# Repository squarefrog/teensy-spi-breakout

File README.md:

# Teensy 3.2 SPI Breakout Board

A 45x42mm breakout board for the [Teensy 3.2](https://www.pjrc.com/teensy/teensy31.html). It features a tonne of `3V` and `GND` pins, as well as 3 header pins for SPI connections. There are smaller more concise breakouts, but I needed something that placed the Teensy's USB port at the top, with 4 decent sized mount points.

As used in my [MIDI Encoder Box](https://github.com/squarefrog/teensy-midi-encoder-box) project.

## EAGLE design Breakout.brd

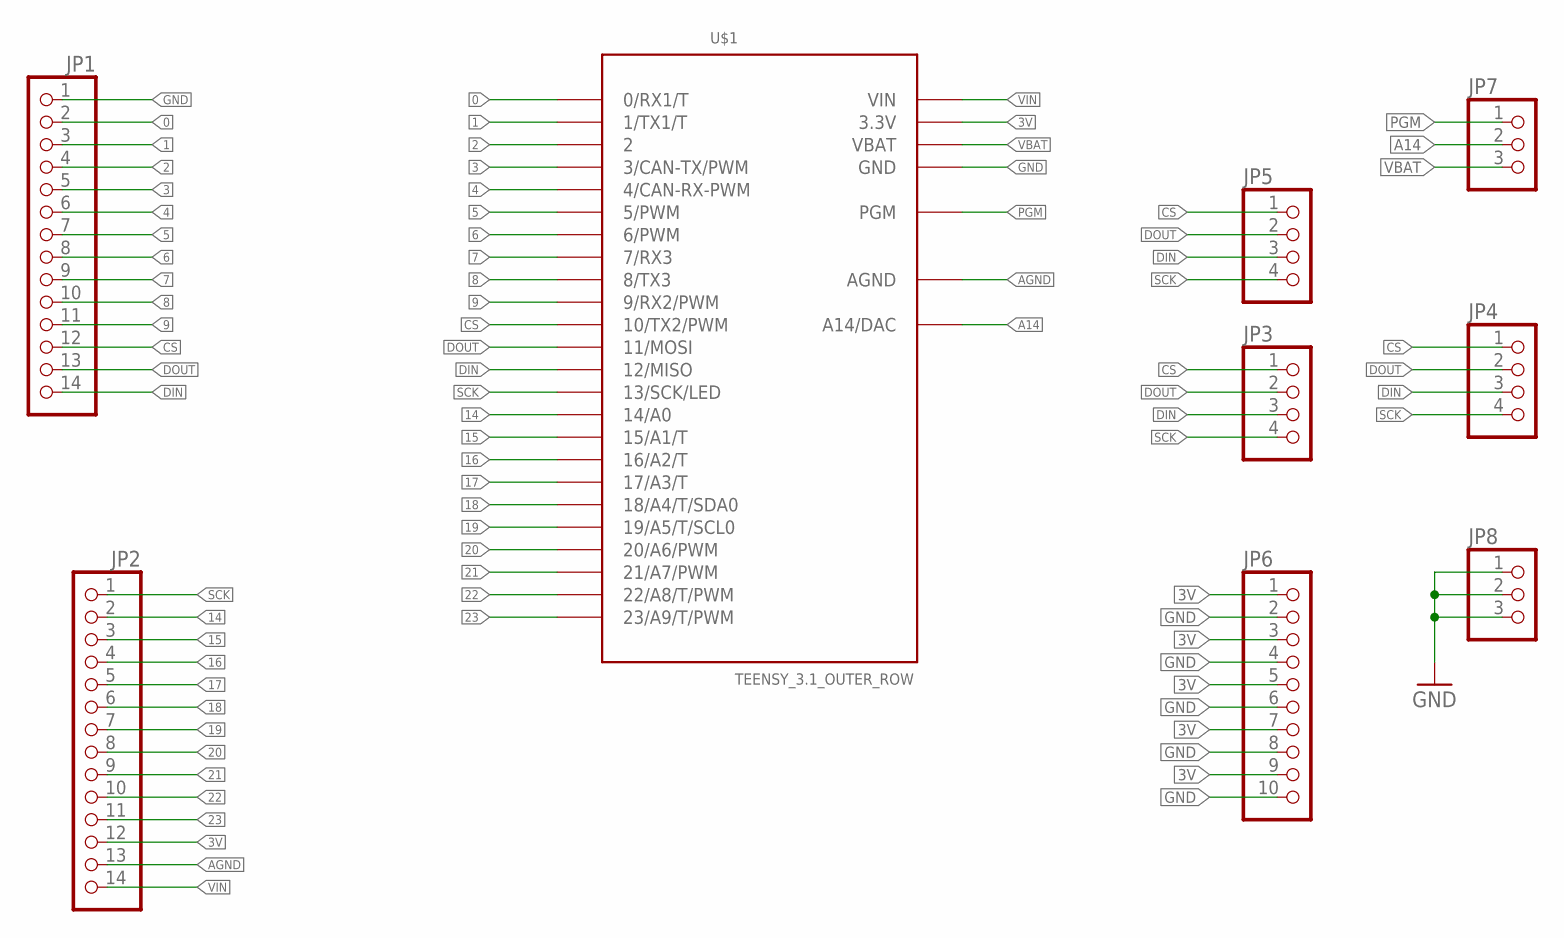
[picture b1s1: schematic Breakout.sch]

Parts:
JP1, JP2: PINHD-1X14; 1X14
JP3, JP4, JP5: PINHD-1X4; 1X04
JP6: PINHD-1X10; 1X10
JP7, JP8: PINHD-1X3; 1X03
U$1: TEENSY_3.1_OUTER_ROW; TEENSY3-OUTER_ROW

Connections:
0: JP1.2, U$1.0 (0/RX1/T)
1: JP1.3, U$1.1 (1/TX1/T)
2: JP1.4, U$1.2
3: JP1.5, U$1.3 (3/CAN-TX/PWM)
3V: JP2.12, JP6.1, JP6.3, JP6.5, JP6.7, JP6.9, U$1.3.3V, U$1.3.3V1 (3.3V)
4: JP1.6, U$1.4 (4/CAN-RX-PWM)
5: JP1.7, U$1.5 (5/PWM)
6: JP1.8, U$1.6 (6/PWM)
7: JP1.9, U$1.7 (7/RX3)
8: JP1.10, U$1.8 (8/TX3)
9: JP1.11, U$1.9 (9/RX2/PWM)
14: JP2.2, U$1.14/A0
15: JP2.3, U$1.15/A1 (15/A1/T)
16: JP2.4, U$1.16/A2 (16/A2/T)
17: JP2.5, U$1.17/A3 (17/A3/T)
18: JP2.6, U$1.18/A4 (18/A4/T/SDA0)
19: JP2.7, U$1.19/A5 (19/A5/T/SCL0)
20: JP2.8, U$1.20/A6 (20/A6/PWM)
21: JP2.9, U$1.21/A7 (21/A7/PWM)
22: JP2.10, U$1.22/A8 (22/A8/T/PWM)
23: JP2.11, U$1.23/A9 (23/A9/T/PWM)
A14: JP7.2, U$1.RESET/DAC (A14/DAC)
AGND: JP2.13, U$1.AGND
CS: JP1.12, JP3.1, JP4.1, JP5.1, U$1.10 (10/TX2/PWM)
DIN: JP1.14, JP3.3, JP4.3, JP5.3, U$1.12 (12/MISO)
DOUT: JP1.13, JP3.2, JP4.2, JP5.2, U$1.11 (11/MOSI)
GND: JP1.1, JP6.2, JP6.4, JP6.6, JP6.8, JP6.10, JP8.1, JP8.2, JP8.3, U$1.GND, U$1.GND1 (GND)
PGM: JP7.1, U$1.PGM
SCK: JP2.1, JP3.4, JP4.4, JP5.4, U$1.13 (13/SCK/LED)
VBAT: JP7.3, U$1.VBAT
VIN: JP2.14, U$1.VIN

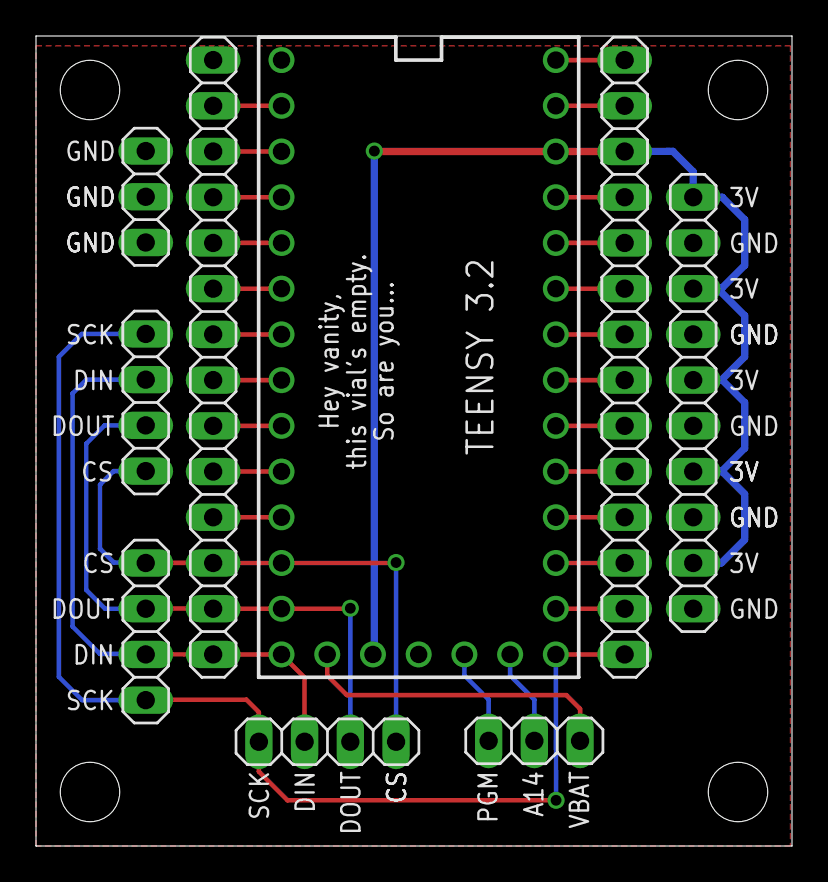
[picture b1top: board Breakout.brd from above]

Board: 2 copper layers, 42.0 x 45.0 mm, 13 parts (0 on the bottom side), 31 nets.

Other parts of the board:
U$2, U$3, U$4, U$5: STAND-OFF

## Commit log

2016-08-24 Nudge layout to fit more squarely on mil grid
2016-08-24 Add ALL the GNDs...
2016-08-24 Fixup ERC
2016-08-24 Add project README
2016-08-24 Add images to README

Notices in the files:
Breakout.brd:
CC BY-SA 4.0
parts and their libraries:
SparkFun-Electromechanical: Licensing: Creative Commons ShareAlike 4.0 International - https://creativecommons.org/licenses/by-sa/4.0
